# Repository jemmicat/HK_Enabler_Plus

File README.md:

HK_Enabler_Plus
===============

Making the Arduino Interface with the IBUS like the HK Enabler

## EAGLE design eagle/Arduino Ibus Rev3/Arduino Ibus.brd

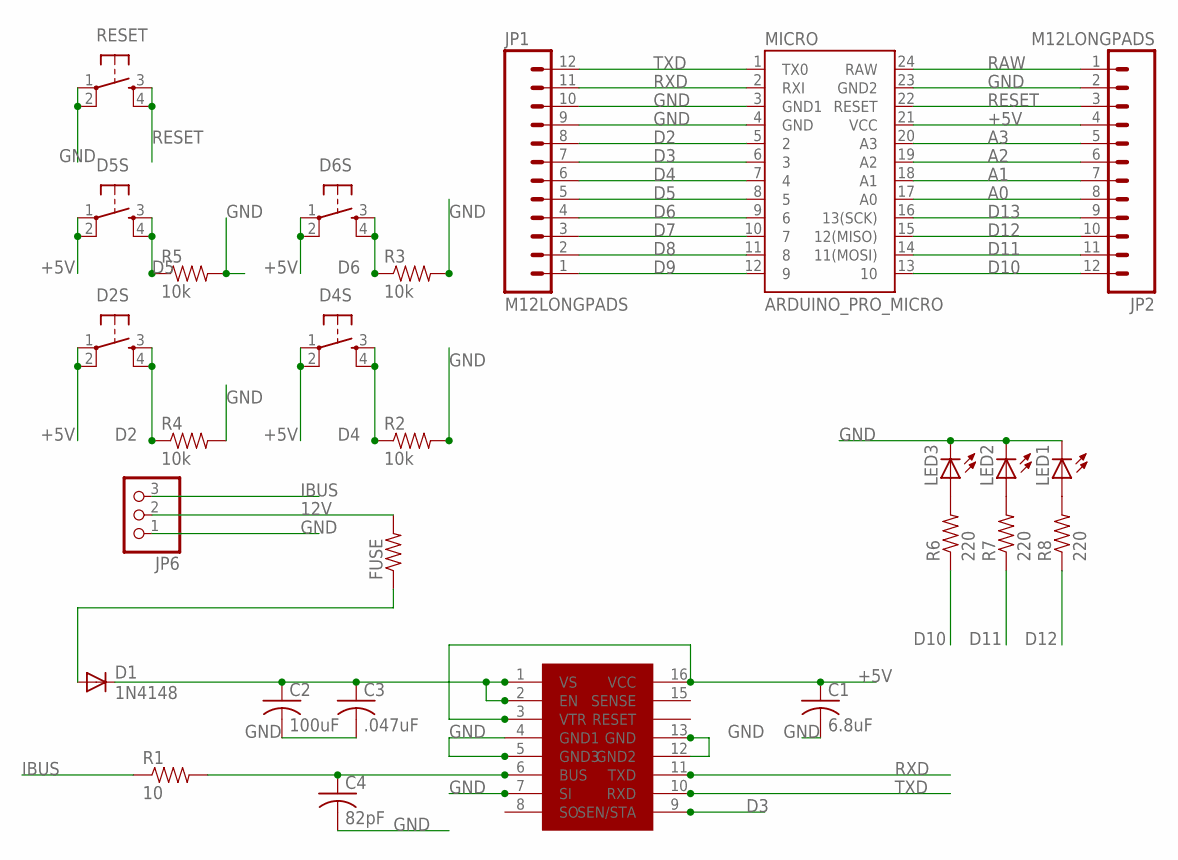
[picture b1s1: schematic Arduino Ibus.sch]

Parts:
C1: 6.8uF; C1206
C2: 100uF; C1206
C3: .047uF; C1206
C4: 82pF; C1206
D1: 1N4148; SMA-DIODE
D2S, D4S, D5S, D6S: TAC_SWITCHPTH; TACTILE-PTH
FUSE: RESISTOR1206; 1206
JP1, JP2: M12LONGPADS; 1X12_LONGPADS
JP6: PINHD-1X3; 1X03
LED1, LED2, LED3: LED1206; LED-1206
MICRO: ARDUINO_PRO_MICRO
R1: 10; 1206
R2, R3, R4, R5: 10k; 1206
R6, R7, R8: 220; 1206
RESET: TAC_SWITCHPTH; TACTILE-PTH
U$1: TH3122; SO16W

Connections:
12V: FUSE.2, JP6.2
+5V: C1.1, D2S.1, D2S.2, D4S.1, D4S.2, D5S.1, D5S.2, D6S.1, D6S.2, JP2.4, MICRO.21 (VCC), U$1.3 (VTR), U$1.16 (VCC)
+12V: D1.A, FUSE.1
A0: JP2.8, MICRO.17 (A0)
A1: JP2.7, MICRO.18 (A1)
A2: JP2.6, MICRO.19 (A2)
A3: JP2.5, MICRO.20 (A3)
D2: D2S.3, D2S.4, JP1.8, MICRO.5 (2), R4.1
D3: JP1.7, MICRO.6 (3), U$1.9 (SEN/STA)
D4: D4S.3, D4S.4, JP1.6, MICRO.7 (4), R2.1
D5: D5S.3, D5S.4, JP1.5, MICRO.8 (5), R5.1
D6: D6S.3, D6S.4, JP1.4, MICRO.9 (6), R3.1
D7: JP1.3, MICRO.10 (7)
D8: JP1.2, MICRO.11 (8)
D9: JP1.1, MICRO.12 (9)
D10: JP2.12, MICRO.13 (10), R6.1
D11: JP2.11, MICRO.14 (11(MOSI)), R7.1
D12: JP2.10, MICRO.15 (12(MISO)), R8.1
D13: JP2.9, MICRO.16 (13(SCK))
GND: C1.2, C2.2, C3.2, C4.2, JP1.9, JP1.10, JP2.2, JP6.1, LED1.C, LED2.C, LED3.C, MICRO.3 (GND1), MICRO.4 (GND), MICRO.23 (GND2), R2.2, R3.2, R4.2, R5.2, RESET.1, RESET.2, U$1.4 (GND1), U$1.5 (GND3), U$1.7 (SI), U$1.12 (GND2), U$1.13 (GND)
IBUS: JP6.3, R1.1
unnamed: LED1.A, R8.2
unnamed: LED2.A, R7.2
unnamed: C2.1, C3.1, D1.C, U$1.1 (VS), U$1.2 (EN)
unnamed: C4.1, R1.2, U$1.6 (BUS)
unnamed: LED3.A, R6.2
RAW: JP2.1, MICRO.24 (RAW)
RESET: JP2.3, MICRO.22 (RESET), RESET.3, RESET.4
RXD: JP1.11, MICRO.2 (RXI), U$1.11 (TXD)
TXD: JP1.12, MICRO.1 (TX0), U$1.10 (RXD)

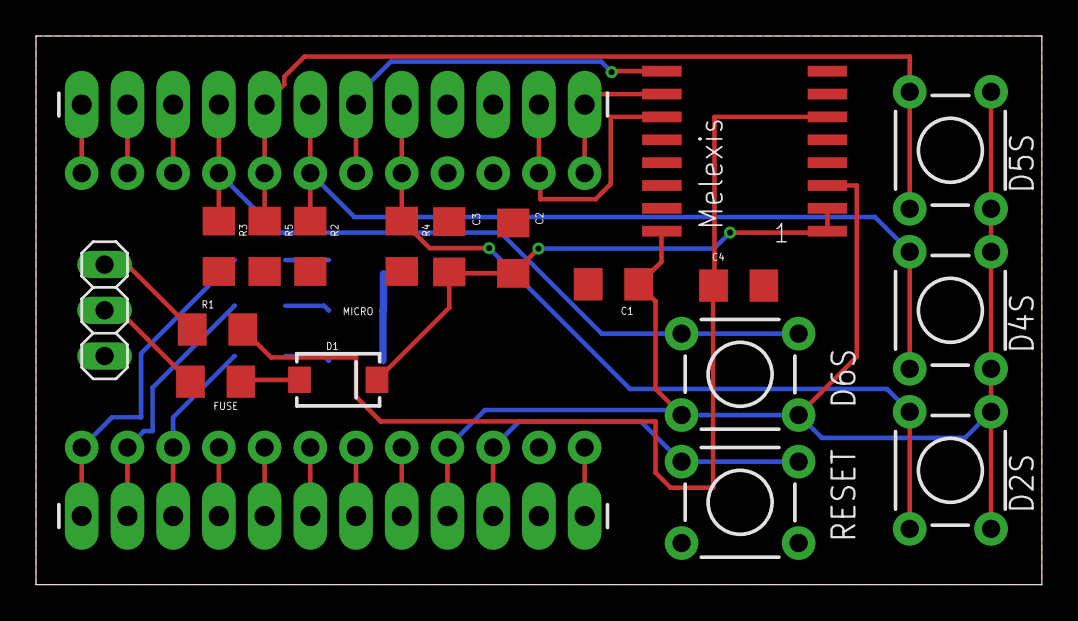
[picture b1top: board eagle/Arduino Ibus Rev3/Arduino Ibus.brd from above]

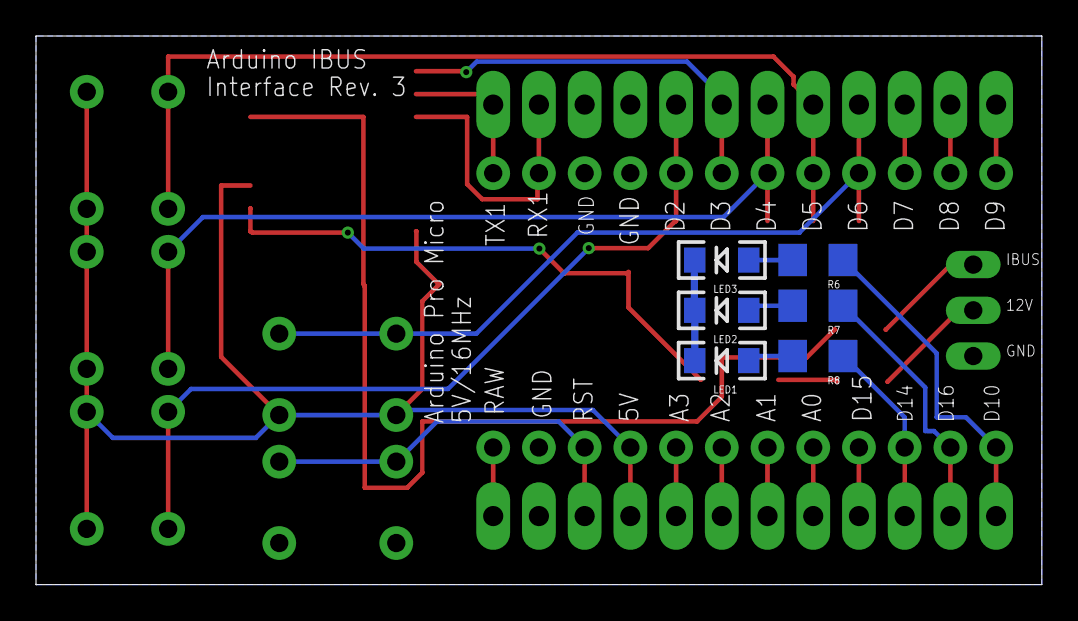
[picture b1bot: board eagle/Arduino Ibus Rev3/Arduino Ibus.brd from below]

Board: 2 copper layers, 55.9 x 30.5 mm, 27 parts (6 on the bottom side), 30 nets.

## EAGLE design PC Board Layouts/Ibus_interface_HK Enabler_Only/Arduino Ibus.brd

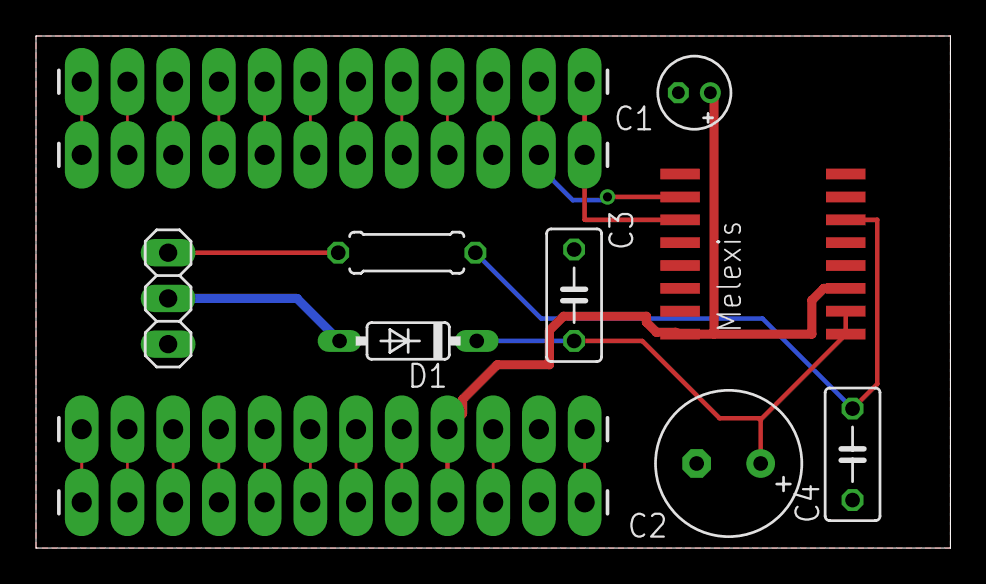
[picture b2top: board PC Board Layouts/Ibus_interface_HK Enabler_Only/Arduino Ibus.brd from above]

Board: 2 copper layers, 50.8 x 28.4 mm, 12 parts (0 on the bottom side), 28 nets.

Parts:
C1: 6.8uF; E1,8-4
C2: 100uF; E3,5-8
C3: .047uF; C050-030X075
C4: 82pF; C050-030X075
D1: 1N4148; DO35-7
JP1, JP2, JP3, JP4: M12LONGPADS; 1X12_LONGPADS
JP6: 1X03
R1: 10; 0207/7
U$1: TH3122; SO16W

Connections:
+5V: C1.+, JP2.4, JP4.4, U$1.3, U$1.16
+12V: D1.A, JP6.2
A0: JP2.8, JP4.8
A1: JP2.7, JP4.7
A2: JP2.6, JP4.6
A3: JP2.5, JP4.5
D2: JP1.8, JP3.8
D3: JP1.7, JP3.7
D4: JP1.6, JP3.6
D5: JP1.5, JP3.5
D6: JP1.4, JP3.4
D7: JP1.3, JP3.3
D8: JP1.2, JP3.2
D9: JP1.1, JP3.1
D10: JP2.12, JP4.12
D14: JP2.10, JP4.10
D15: JP2.9, JP4.9
D16: JP2.11, JP4.11
GND: C1.-, C2.-, C3.2, C4.2, JP2.2, JP4.2, JP6.1, U$1.4, U$1.5, U$1.9, U$1.12, U$1.13
IBUS: JP6.3, R1.1
unnamed: JP1.10, JP3.10
unnamed: JP1.9, JP3.9
unnamed: C2.+, C3.1, D1.C, U$1.1, U$1.2
unnamed: C4.1, R1.2, U$1.6
RAW: JP2.1, JP4.1
RST: JP2.3, JP4.3
RX1: JP1.11, JP3.11, U$1.10
TX1: JP1.12, JP3.12, U$1.11

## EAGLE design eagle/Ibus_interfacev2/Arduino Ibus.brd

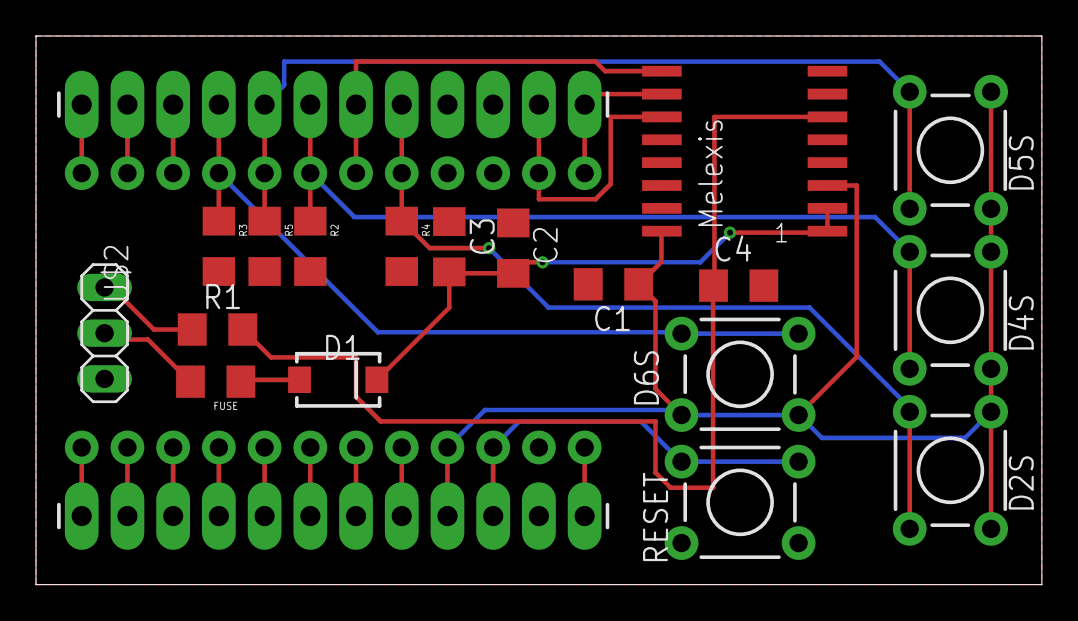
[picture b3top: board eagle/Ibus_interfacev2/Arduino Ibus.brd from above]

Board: 2 copper layers, 55.9 x 30.5 mm, 21 parts (0 on the bottom side), 27 nets.

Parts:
C1: 6.8uF; C1206
C2: 100uF; C1206
C3: .047uF; C1206
C4: 82pF; C1206
D1: 1N4148; SMA-DIODE
D2S, D4S, D5S, D6S: TACTILE-PTH
FUSE: 1206
JP1, JP2: M12LONGPADS; 1X12_LONGPADS
JP6: 1X03
R1: 10; 1206
R2, R3, R4, R5: 10k; 1206
RESET: TACTILE-PTH
U$1: TH3122; SO16W
U$2: ARDUINO_PRO_MICRO

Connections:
12V: FUSE.2, JP6.2
+5V: C1.1, D2S.1, D2S.2, D4S.1, D4S.2, D5S.1, D5S.2, D6S.1, D6S.2, JP2.4, U$1.3, U$1.16, U$2.21
+12V: D1.A, FUSE.1
A0: JP2.8, U$2.17
A1: JP2.7, U$2.18
A2: JP2.6, U$2.19
A3: JP2.5, U$2.20
D2: D2S.3, D2S.4, JP1.8, R4.1, U$2.5
D3: JP1.7, U$1.9, U$2.6
D4: D4S.3, D4S.4, JP1.6, R2.1, U$2.7
D5: D5S.3, D5S.4, JP1.5, R5.1, U$2.8
D6: D6S.3, D6S.4, JP1.4, R3.1, U$2.9
D7: JP1.3, U$2.10
D8: JP1.2, U$2.11
D9: JP1.1, U$2.12
D10: JP2.12, U$2.13
D11: JP2.11, U$2.14
D12: JP2.10, U$2.15
D13: JP2.9, U$2.16
GND: C1.2, C2.2, C3.2, C4.2, JP1.9, JP1.10, JP2.2, JP6.1, R2.2, R3.2, R4.2, R5.2, RESET.1, RESET.2, U$1.4, U$1.5, U$1.7, U$1.12, U$1.13, U$2.3, U$2.4, U$2.23
IBUS: JP6.3, R1.1
unnamed: C2.1, C3.1, D1.C, U$1.1, U$1.2
unnamed: C4.1, R1.2, U$1.6
RAW: JP2.1, U$2.24
RESET: JP2.3, RESET.3, RESET.4, U$2.22
RXD: JP1.11, U$1.11, U$2.2
TXD: JP1.12, U$1.10, U$2.1

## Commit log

2013-11-19 Added
2013-11-25 Finished PC Board
2013-11-25 PC Board Schematic
2013-11-25 Added other code
2013-11-26 Reorganized Folders and added files
2013-11-26 Added required Adafruit library
2013-11-29 Changed Brute Force PCB to be smaller with no options
2013-11-30 working on HK plus
2013-12-01 Added SerLCD library
2013-12-02 Corrected libraries and Added Files to HK Enabler Plus
2013-12-03 Added BOM And Part Numbers
2013-12-03 Updated Code
2013-12-05 IMU file
2013-12-06 Moved Ordering Files Around
2013-12-06 Updated BOM With Part Callouts
2013-12-11 BOM update
2013-12-14 bluetooth
2013-12-18 work on program
2013-12-30 added more delay before sending codes
2014-01-01 changed delays
2014-01-02 Added Files
2014-01-30 Added cloned directory from blalor
2014-02-17 Added retries
2014-02-20 added code
2014-03-02 retries
2014-05-29 changed retry method
2014-06-16 Using SENSTA Line Now to detect collisions
2014-06-16 Changed display settings

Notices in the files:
parts and their libraries:
SparkFun-Connectors: Licensing: CC v3.0 Share-Alike You are welcome to use this library for commercial purposes.
